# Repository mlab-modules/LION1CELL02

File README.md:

# LION1CELL02 - Single-cell Li-Ion BMS power supply with I2C interface 

Integrated battery management solution for 18650 Li-ion batteries. It can measure remaining energy in the battery, perform a charging cycle from a USB-C power source, and protect batteries against overvoltage or overdraining conditions.

## Features 

  * Charging, balancing, termination (temperature protected)
  * Gas-gauging (temperature compensated)
  * Over-voltage protection
  * Over-current protection
  * Under-voltage is not protected - the module is constructed to power the device until battery death 

## Connection

The module could communicate on the I2C or HDQ bus.

| Mark | signal| Description |
|------|-----|---|
|1 | PG |	|
|2 | STAT2 | |
|3 | GND |	|
|4 | CE | |
|5 | STAT1 | |
|6 | CMODE | |

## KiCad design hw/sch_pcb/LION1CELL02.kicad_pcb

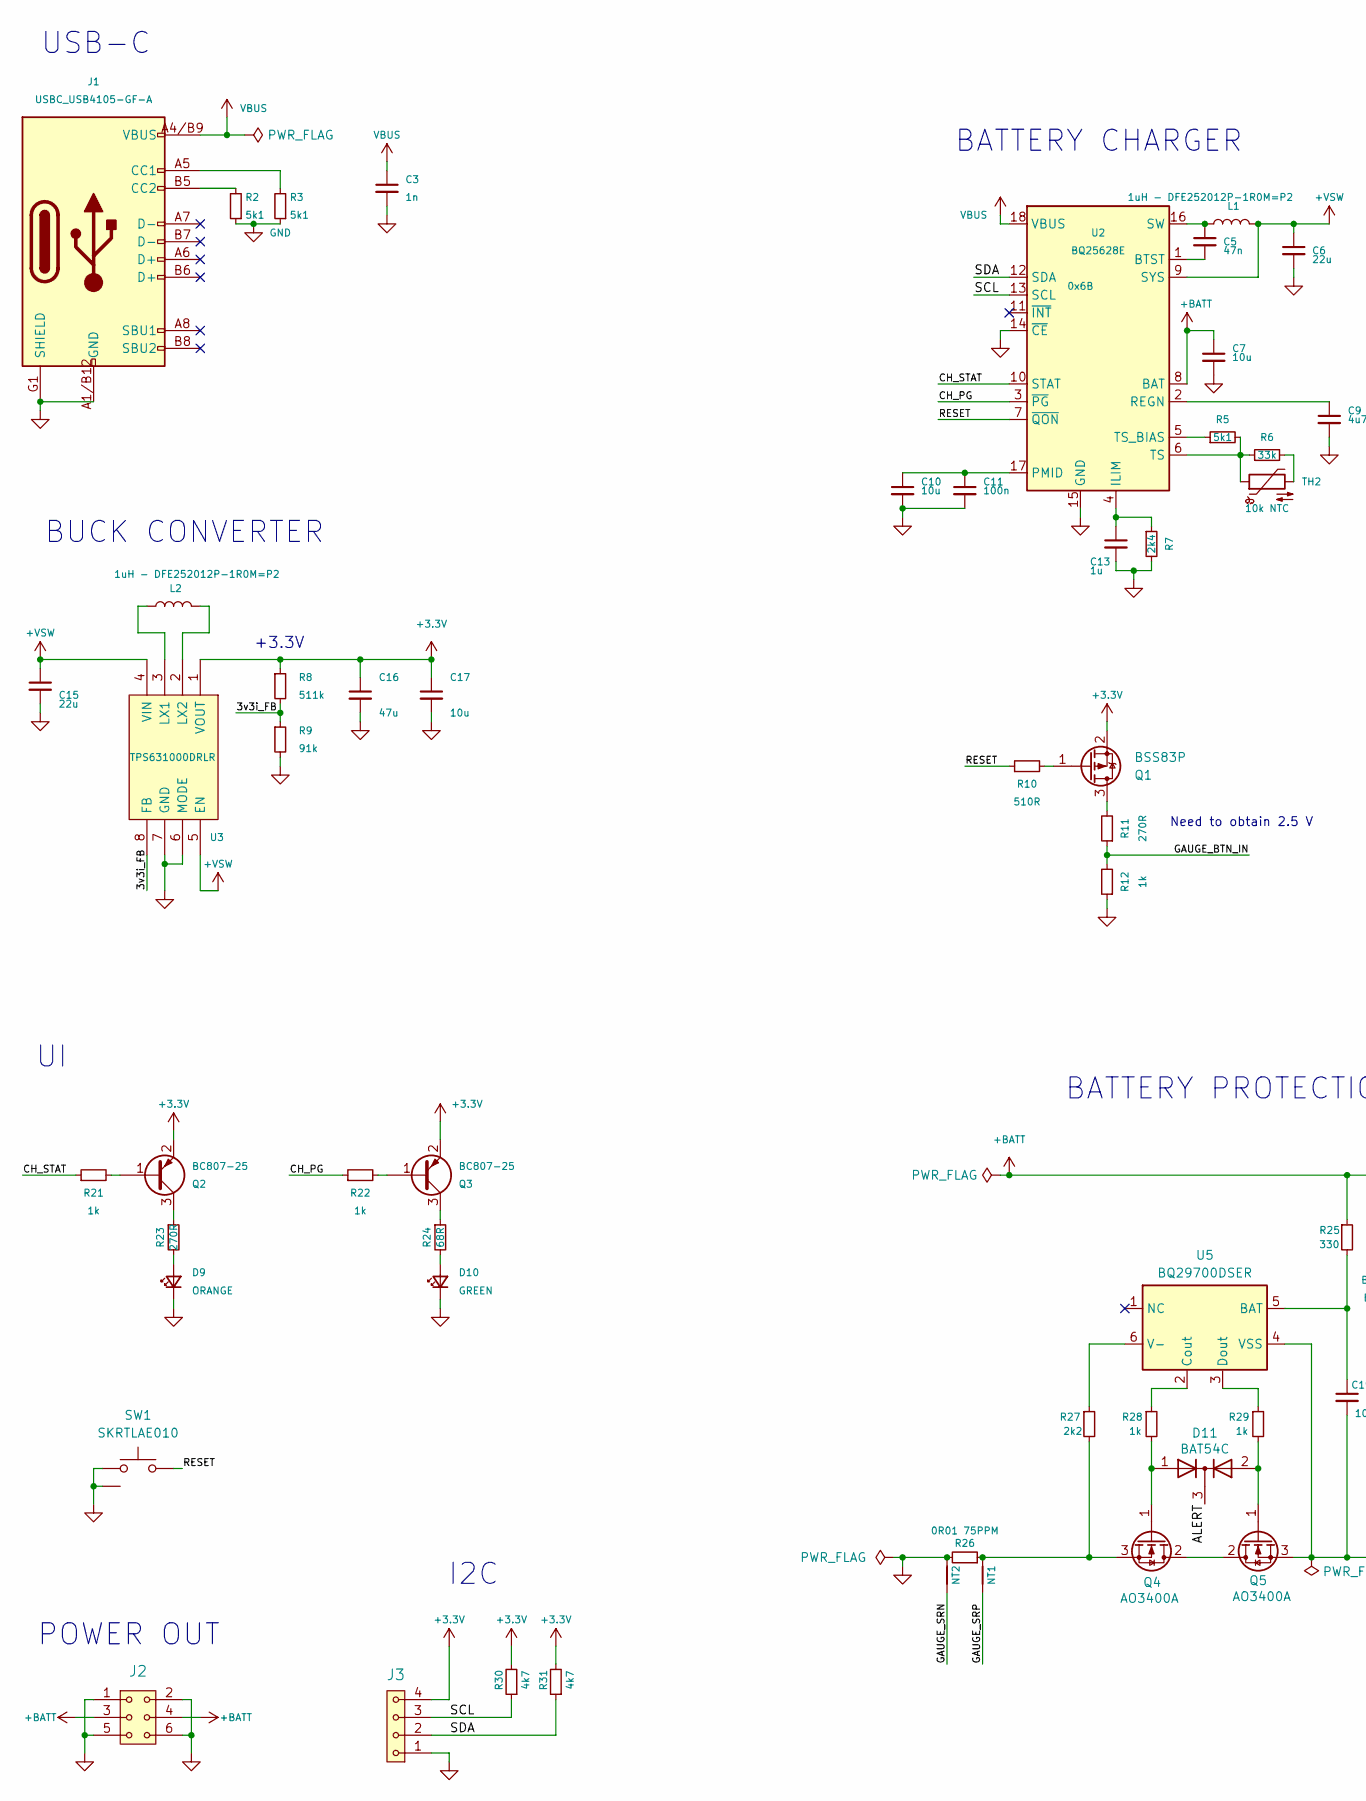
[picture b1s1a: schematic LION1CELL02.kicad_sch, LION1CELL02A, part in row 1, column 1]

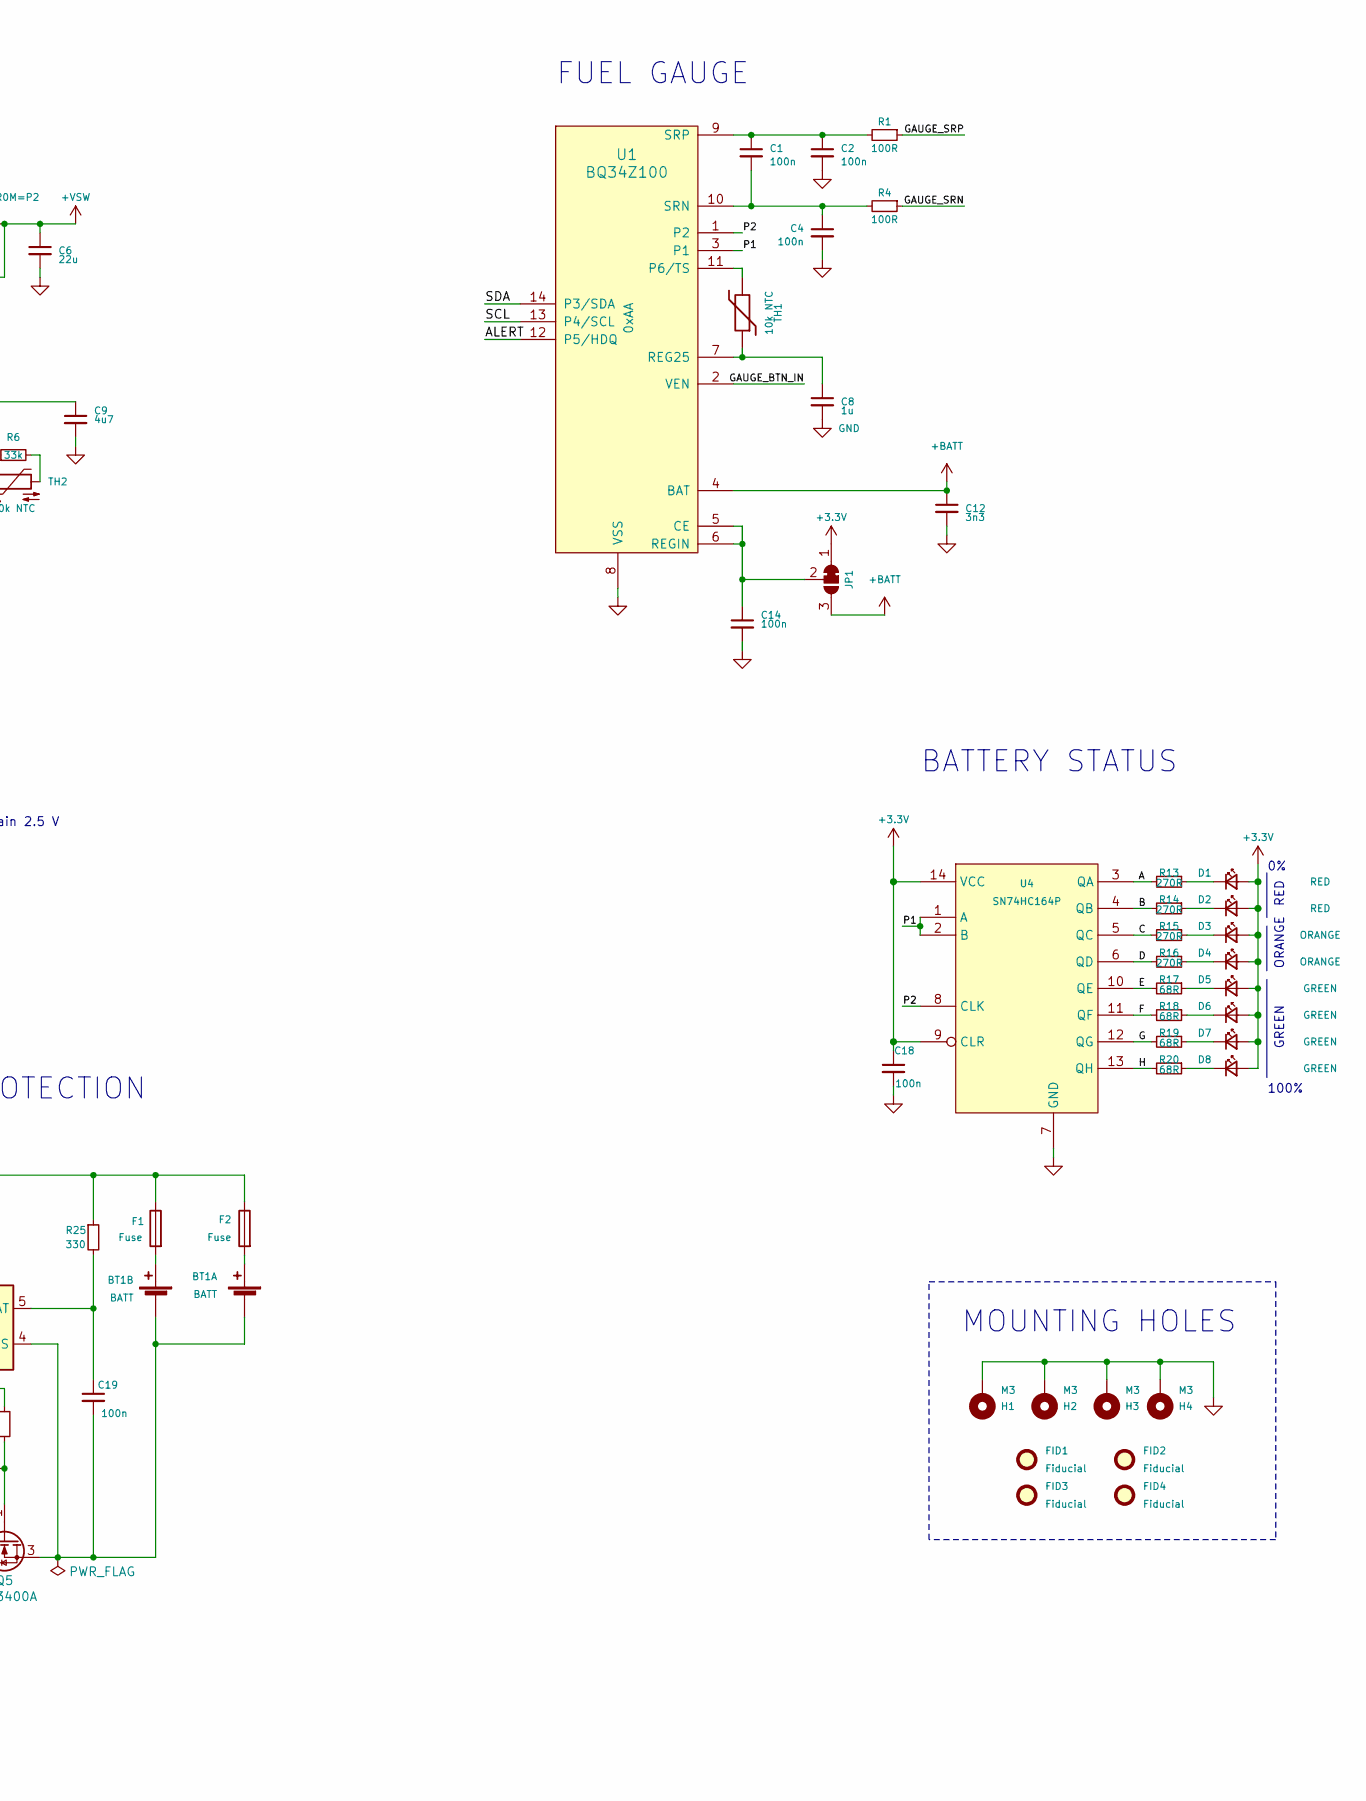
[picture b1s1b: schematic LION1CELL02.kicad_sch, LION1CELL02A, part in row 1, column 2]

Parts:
BT1: BATT; BAT_BK-18650-PC4
C1, C2, C4, C11, C14, C18, C19: 100n; C_0805_2012Metric
C3: 1n; C_0805_2012Metric; MPN C0805 1u
C5: 47n; C_0805_2012Metric
C6, C15: 22u; C_0805_2012Metric
C7, C10, C17: 10u; C_0805_2012Metric
C8, C13: 1u; C_0805_2012Metric
C9: 4u7; C_0805_2012Metric
C12: 3n3; C_0805_2012Metric
C16: 47u; C_0805_2012Metric
D1, D2: RED; SMD_LED_RIGHT_KINGBRIGHT_1605
D3, D4, D9: ORANGE; SMD_LED_RIGHT_KINGBRIGHT_1605
D5, D6, D7, D8, D10: GREEN; SMD_LED_RIGHT_KINGBRIGHT_1605
D11: BAT54C; SOT-23
F1, F2: Fuse; Fuseholder_Littelfuse_Nano2_154x
FID1, FID2, FID3, FID4: Fiducial; Fiducial_1mm_Mask2mm
H1, H2, H3, H4: M3; MountingHole_3mm
J1: USBC_USB4105-GF-A; USBC GCT_USB4105-GF-A; MPN USB4105-GF-A
J2: HEADER_2x03; PinHeader_2x03_P2.54mm_Vertical
J3: HEADER_1x04; PinHeader_1x04_P2.54mm_Horizontal
JP1: Jumper_3_Bridged12; SolderJumper-3_P1.3mm_Bridged2Bar12_RoundedPad1.0x1.5mm
L1, L2: 1uH - DFE252012P-1R0M=P2; L_1008_2520Metric
NT1, NT2: NetTie_2; NetTie-2_SMD_Pad0.5mm
Q1: BSS83P; SOT-23
Q2, Q3: BC807-25; SOT-23-3
Q4, Q5: AO3400A; SOT-23-3
R1, R4: 100R; R_0805_2012Metric
R2, R3, R5: 5k1; R_0805_2012Metric
R6: 33k; R_0805_2012Metric
R7: 2k4; R_0805_2012Metric
R8: 511k; R_0805_2012Metric
R9: 91k; R_0805_2012Metric
R10: 510R; R_0805_2012Metric
R11, R13, R14, R15, R16, R23: 270R; R_0805_2012Metric
R12, R21, R22, R28, R29: 1k; R_0805_2012Metric
R17, R18, R19, R20, R24: 68R; R_0805_2012Metric
R25: 330; R_0805_2012Metric
R26: 0R01 75PPM; R_2512_6332Metric
R27: 2k2; R_0805_2012Metric
R30, R31: 4k7; R_0805_2012Metric
SW1: SKRTLAE010; SKRT
TH1, TH2: 10k NTC; R_0805_2012Metric
U1: BQ34Z100; TSSOP-14_4.4x5mm_Pitch0.65mm
U2: BQ25628E; Texas_S-WQFN-HR-18
U3: TPS631000DRLR; SOT-583-8; Mouser Part Number 595-TPS631000DRLR
U4: SN74HC164P; TSSOP-14_4.4x5mm_P0.65mm
U5: BQ29700DSER; WSON-6_1.5x1.5mm_P0.5mm

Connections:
+3.3V: C16.1, C17.1, C18.1, D1.2 (A), D2.2 (A), D3.2 (A), D4.2 (A), D5.2 (A), D6.2 (A), D7.2 (A), D8.2 (A), J3.4, JP1.1 (A), Q1.2 (S), Q2.2 (E), Q3.2 (E), R8.1, R30.2, R31.2, U3.1 (VOUT), U4.9 (CLR), U4.14 (VCC)
+BATT: C7.1, C12.1, F1.1, F2.1, J2.3, J2.4, JP1.3 (B), R25.1, U1.4 (BAT), U2.8 (BAT)
+VSW: C6.1, C15.1, L1.2, U2.9 (SYS), U3.4 (VIN), U3.5 (EN)
/3v3i_FB: R8.2, R9.1, U3.8 (FB)
/A: R13.2, U4.3 (QA)
/ALERT: D11.3 (K), U1.12 (P5/HDQ)
/B: R14.2, U4.4 (QB)
/C: R15.2, U4.5 (QC)
/CH_PG: R22.1, U2.3 (~PG)
/CH_STAT: R21.1, U2.10 (STAT)
/D: R16.2, U4.6 (QD)
/E: R17.2, U4.10 (QE)
/F: R18.2, U4.11 (QF)
/G: R19.2, U4.12 (QG)
/GAUGE_BTN_IN: R11.1, R12.2, U1.2 (VEN)
/GAUGE_SRN: NT2.1, R4.1
/GAUGE_SRP: NT1.1, R1.1
/H: R20.2, U4.13 (QH)
/P1: U1.3 (P1), U4.1 (A), U4.2 (B)
/P2: U1.1 (P2), U4.8 (CLK)
/RESET: R10.1, SW1.1, U2.7 (~QON)
/SCL: J3.3, R30.1, U1.13 (P4/SCL), U2.13 (SCL)
/SDA: J3.2, R31.1, U1.14 (P3/SDA), U2.12 (SDA)
GND: C2.2, C3.2, C4.2, C6.2, C7.2, C8.2, C9.2, C10.2, C11.2, C12.2, C13.2, C14.2, C15.2, C16.2, C17.2, C18.2, D9.1 (K), D10.1 (K), H1.1 (1_1), H2.1 (1_1), H3.1 (1_1), H4.1 (1_1), J1.A1/B12 (GND), J1.B1/A12 (GND), J1.G1 (SHIELD), J1.G2 (SHIELD), J1.G3 (SHIELD), J1.G4 (SHIELD), J2.1, J2.2, J2.5, J2.6, J3.1, NT2.2, R2.1, R3.1, R7.2, R9.2, R12.1, R26.2, SW1.2, SW1.GND (SHIELD), U1.8 (VSS), U2.14 (~CE), U2.15 (GND), U3.6 (MODE), U3.7 (GND), U4.7 (GND)
unnamed: BT1.1+ (+), F2.2
unnamed: BT1.1- (-), BT1.2- (-), C19.2, Q5.3 (S), U5.4 (VSS)
unnamed: BT1.2+ (+), F1.2
unnamed: D1.1 (K), R13.1
unnamed: D2.1 (K), R14.1
unnamed: D3.1 (K), R15.1
unnamed: D4.1 (K), R16.1
unnamed: D5.1 (K), R17.1
unnamed: D6.1 (K), R18.1
unnamed: D7.1 (K), R19.1
unnamed: D8.1 (K), R20.1
unnamed: D9.2 (A), R23.2
unnamed: D10.2 (A), R24.2
unnamed: J1.A5 (CC1), R3.2
unnamed: J1.B5 (CC2), R2.2
unnamed: C14.1, JP1.2 (C), U1.5 (CE), U1.6 (REGIN)
unnamed: Q1.3 (D), R11.2
unnamed: Q1.1 (G), R10.2
unnamed: Q2.1 (B), R21.2
unnamed: Q2.3 (C), R23.1
unnamed: Q3.1 (B), R22.2
unnamed: Q3.3 (C), R24.1
unnamed: Q4.2 (D), Q5.2 (D)
unnamed: D11.1 (A), Q4.1 (G), R28.2
unnamed: NT1.2, Q4.3 (S), R26.1, R27.2
unnamed: D11.2 (A), Q5.1 (G), R29.2
unnamed: R6.2, TH2.2
unnamed: TH1.2, U1.11 (P6/TS)
unnamed: C8.1, TH1.1, U1.7 (REG25)
unnamed: C1.2, C4.1, R4.2, U1.10 (SRN)
unnamed: C1.1, C2.1, R1.2, U1.9 (SRP)
unnamed: C5.2, U2.1 (BTST)
unnamed: C13.1, R7.1, U2.4 (ILIM)
unnamed: C10.1, C11.1, U2.17 (PMID)
unnamed: C9.1, U2.2 (REGN)
unnamed: C5.1, L1.1, U2.16 (SW)
unnamed: R5.2, R6.1, TH2.1, U2.6 (TS)
unnamed: R5.1, U2.5 (TS_BIAS)
unnamed: L2.1, U3.3 (LX1)
unnamed: L2.2, U3.2 (LX2)
unnamed: C19.1, R25.2, U5.5 (BAT)
unnamed: R28.1, U5.2 (Cout)
unnamed: R29.1, U5.3 (Dout)
unnamed: R27.1, U5.6 (V-)
VBUS: C3.1, J1.A4/B9 (VBUS), J1.B4/A9 (VBUS), U2.18 (VBUS)

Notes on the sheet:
+3.3V
BATTERY STATUS
POWER OUT
ORANGE
Need to obtain 2.5 V
I2C
BUCK CONVERTER
RED
100%
MOUNTING HOLES
USB-C
BATTERY PROTECTION
FUEL GAUGE
BATTERY CHARGER
GREEN

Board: 2 copper layers, 93 parts (55 on the bottom side), 69 nets, no tracks yet.

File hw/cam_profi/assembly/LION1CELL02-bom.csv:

Component,Description,Part,References,Value,Footprint,Quantity Per PCB,Datasheet,ust_id,mfpn,mpn,sim.pins,sim.device,sim.type,i2c,height,mouser part number,mouser price/stock,manufacturer_name,manufacturer_part_number
1,Single-cell battery,2xBATT,BT1,BATT,BAT_BK-18650-PC4,1,~,5c70984412875079b91f87e9,,,,,,,,,,,
2,"Unpolarized capacitor, small symbol",C_Small,C3,1n,C_0805_2012Metric,1,~,5c70984712875079b91f8b45,C0805 1u,C0805 1u,,,,,,,,,
3,"Unpolarized capacitor, small symbol",C_Small,C12,3n3,C_0805_2012Metric,1,~,5c70984712875079b91f8b47,,,,,,,,,,,
4,"Unpolarized capacitor, small symbol",C_Small,C5,47n,C_0805_2012Metric,1,~,65482046462c6d9e72056b98,,,,,,,,,,,
5,"Unpolarized capacitor, small symbol",C_Small,C1C2C4C11C14C18C19,100n,C_0805_2012Metric,7,~,5c70984712875079b91f8b4c,,,,,,,,,,,
6,"Unpolarized capacitor, small symbol",C_Small,C8C13,1u,C_0805_2012Metric,2,~,5c70984712875079b91f8b50,,,,,,,,,,,
7,"Unpolarized capacitor, small symbol",C_Small,C9,4u7,C_0805_2012Metric,1,~,5c70984712875079b91f8b52,,,,,,,,,,,
8,"Unpolarized capacitor, small symbol",C_Small,C7C10C17,10u,C_0805_2012Metric,3,~,5c70984712875079b91f8b53,,,,,,,,,,,
9,"Unpolarized capacitor, small symbol",C_Small,C6C15,22u,C_0805_2012Metric,2,~,650b58f1462c6d9e7205463b,,,,,,,,,,,
10,"Unpolarized capacitor, small symbol",C_Small,C16,47u,C_0805_2012Metric,1,~,5c70984812875079b91f8bbf,,,,,,,,,,,
11,"Light emitting diode, small symbol",LED_Small,D5D6D7D8D10,GREEN,SMD_LED_RIGHT_KINGBRIGHT_1605,5,~,65481f0c462c6d9e72056b3d,,,1=K 2=A,,,,,,,,
12,"Light emitting diode, small symbol",LED_Small,D3D4D9,ORANGE,SMD_LED_RIGHT_KINGBRIGHT_1605,3,~,65481fdd462c6d9e72056b6a,,,1=K 2=A,,,,,,,,
13,"Light emitting diode, small symbol",LED_Small,D1D2,RED,SMD_LED_RIGHT_KINGBRIGHT_1605,2,~,65481f96462c6d9e72056b54,,,1=K 2=A,,,,,,,,
14,Fuse,Fuse,F1F2,Fuse,Fuseholder_Littelfuse_Nano2_154x,2,~,5c70984512875079b91f88d8,,,,,,,,,,,
15,1x04 2.54 mm pitch header,HEADER_1x04,J3,HEADER_1x04,PinHeader_1x04_P2.54mm_Horizontal,1,,,,,,,,,,,,,
16,2x03 2.54 mm pitch header,HEADER_2x03,J2,HEADER_2x03,PinHeader_2x03_P2.54mm_Vertical,1,,,,,,,,,,,,,
17,USB 2.0-only Type-C Receptacle connector,USBC_USB4105-GF-A,J1,USBC_USB4105-GF-A,USBC GCT_USB4105-GF-A,1,,5fa0f94612875025b397795e,USB4105-GF-A,USB4105-GF-A,,,,,,,,,
18,Inductor,L,L1L2,1uH - DFE252012P-1R0M=P2,L_1008_2520Metric,2,~,650b5977462c6d9e72054656,,,,,,,,,,,
19,"PNP transistor, base/emitter/collector",Q_PNP_BEC,Q2Q3,BC807-25,SOT-23-3,2,~,5c70984712875079b91f8aeb,,,1=C 2=B 3=E,NPN,GUMMELPOON,,,,,,
20,"P-MOSFET transistor, gate/source/drain",Q_PMOS_GSD,Q1,BSS83P,SOT-23,1,~,5c70984712875079b91f8ae6,,,,,,,,,,,
21,"N-MOSFET transistor, gate/drain/source",Q_NMOS_GDS,Q4Q5,SI2302A-TP,SOT-23-3,2,~,,,,,,,,,,,,
22,"Resistor, small symbol",R_Small,R17R18R19R20R24,68R,R_0805_2012Metric,5,~,5c70984512875079b91f8975,,,,,,,,,,,
23,"Resistor, small symbol",R_Small,R1R4,100R,R_0805_2012Metric,2,~,5c70984512875079b91f8977,,,,,,,,,,,
24,"Resistor, small symbol",R_Small,R11R13R14R15R16R23,270R,R_0805_2012Metric,6,~,5c70984512875079b91f8983,,,,,,,,,,,
25,"Resistor, small symbol",R_Small,R25,330,R_0805_2012Metric,1,~,,,,,,,,,,,,
26,"Resistor, small symbol",R_Small,R10,510R,R_0805_2012Metric,1,~,5c70984512875079b91f8988,,,,,,,,,,,
27,"Resistor, small symbol",R_Small,R12R21R22,1k,R_0805_2012Metric,3,~,5c70984512875079b91f898c,,,,,,,,,,,
28,"Resistor, small symbol",R_Small,R27,2k2,R_0805_2012Metric,1,~,,,,,,,,,,,,
29,"Resistor, small symbol",R_Small,R7,2k4,R_0805_2012Metric,1,~,5c70984612875079b91f8991,,,,,,,,,,,
30,"Resistor, small symbol",R_Small,R30R31,4k7,R_0805_2012Metric,2,~,5c70984512875079b91f898c,,,,,,,,,,,
31,"Resistor, small symbol",R_Small,R2R3R5,5k1,R_0805_2012Metric,3,~,5fa0fc3e12875025b3977997,,,,,,,,,,,
32,"Resistor, small symbol",R_Small,R6,33k,R_0805_2012Metric,1,~,5c70984712875079b91f8a8a,,,,,,,,,,,
33,"Resistor, small symbol",R_Small,R9,91k,R_0805_2012Metric,1,~,5c70984712875079b91f8a95,,,,,,,,,,,
34,"Resistor, small symbol",R_Small,R8,511k,R_0805_2012Metric,1,~,650b5a43462c6d9e7205468e,,,,,,,,,,,
35,"Resistor, small symbol",R_Small,R26,0R01 75PPM,R_2512_6332Metric,1,~,5c70984712875079b91f8abf,,,,,,,,,,,
36,"Push button switch, generic, two pins",SW_Push_shield,SW1,SKRTLAE010,SKRT,1,~,,,,,,,,,,,,
37,Temperature dependent resistor,Thermistor,TH1,10k NTC,R_0805_2012Metric,1,~,5c70984712875079b91f8ac5,,,,,,,,,,,
38,"Temperature dependent resistor, negative temperature coefficient",Thermistor_NTC,TH2,10k NTC,R_0805_2012Metric,1,~,5c70984712875079b91f8ac5,,,,,,,,,,,
39,"BQ25628E I2C Controlled 1-Cell, 2-A, Maximum 18-V Input, Buck Battery Charger withNVDC Power Path Management",BQ25628E,U2,BQ25628E,Texas_S-WQFN-HR-18,1,https://www.ti.com/lit/ds/symlink/bq25628e.pdf,65481a71462c6d9e72056aa4,,,,,,0x6B,,,,,
40,Voltage and Current Protection for Single-Cell Li-Ion and Li-Polymer Batteries,BQ297xy,U5,BQ29700DSER,WSON-6_1.5x1.5mm_P0.5mm,1,http://www.ti.com/lit/ds/symlink/bq2970.pdf,,,,,,,,,,,,
41,,BQ34Z100,U1,BQ34Z100,TSSOP-14_4.4x5mm_Pitch0.65mm,1,https://www.ti.com/lit/ds/symlink/bq34z100-g1.pdf,5c70984612875079b91f89c3,,,,,,0xAA,"1,2",,,,
42,,SN74HC164D,U4,SN74HC164P,TSSOP-14_4.4x5mm_P0.65mm,1,https://www.ti.com/lit/ds/symlink/sn74hc164.pdf,6559399f95a79cc5ac40a0a6,,,,,,,,,,,
43,"Switching Voltage Regulators 1.5-A output current, high power density buck-boost converter",TPS631000DRLR,U3,TPS631000DRLR,SOT-583-8,1,https://www.ti.com/lit/ds/symlink/tps631000.pdf?ts=1652152702265,63de5ae4ae0b2d5aa05e2714,,,,,,,0.5,595-TPS631000DRLR,https://www.mouser.co.uk/ProductDetail/Texas-Instruments/TPS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,Texas Instruments,TPS631000DRLR

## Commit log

2023-04-13 schematics updated
2023-04-13 Update actions products
2023-04-13 minor changes
2023-05-25 automated commit; add github actions
2023-05-25 Update metadata files
2023-05-28 Update workflow files
2023-07-05 automated commit; rename source files to new naming convence
2023-09-16 Update image to image_title
2023-09-16 Update status
2024-07-17 Update kicad project to version 8.
2025-11-30 Cleanup repository. Update project to KiCADv9.
2026-01-14 Update schematics
2026-01-16 Repository cleanup.
2026-01-17 Batery protection update
2026-01-17 Battery pack update
2026-01-17 Battery protection update
2026-01-17 Update pcb
2026-01-18 Update sch
2026-01-25 Pridani ochrany proti prehrati pres alert pin
2026-05-06 Move sensing resistor bellow protection transistors.
2026-05-15 Update workflow and submodule to KiCAD 10.
2026-05-15 Automatic update of KiCAD outputs
2026-05-15 Update submodule.
2026-05-22 Fix termistor unconnection https://github.com/mlab-modules/BATDATUNIT01/issues/16
